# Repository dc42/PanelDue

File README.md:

PanelDue
========

This is the OLD source code for firmware versions 1.15x and earlier to run the PanelDue 3D printer user interface board. Source code for firmware versions 1.16 and later is in repository PanelDueFirmware, see https://github.com/dc42/PanelDueFirmware.

Build instructions: load file PanelDue.cppproj into Atmel Studio 7.0. For those wishing to build it under operating systems other than Windows, it should not be difficult to port it to Eclipse. The only libraries needed that are not included in this repository are the GCC toolchain libraries for the SAM3S.

Static analysis: parts of the firmware are formally verified using Escher C++ Verifier, hence the design-by-contract and other annotations. File ecv.h defines macros that make these annotations invisible to compilers.

Firmware upload instructions: see http://miscsolutions.wordpress.com/paneldue/

Licence and copyright
=====================

Copyright (c) 2015 Escher Technologies Limited. Licensed under the Creative Commons Attribution-NonCommercial 4.0 license. See https://creativecommons.org/licenses/by-nc/4.0/legalcode for a copy. Some parts of the firmware (c) Henning Karlsen. Some parts of the firmware (c) Atmel Inc.

Submitting pull requests
========================

I will only consider pull requests that meet the following standards:
- the code must compile warning-free, with very few exceptions
- existing design-by-contract annotations must be preserved, and contracts should be added for any new functions. Please asked for a copy of eCv++ Free Edition if you plan on making substantial changes.
- the coding style must be adhered to

Acknowledgements
================

Henning Karlsen - for the original versions of the TFT display driver, see http://www.henningkarlsen.com/electronics/
Atmel - for the Atmel Software Framework, which made programming the ATSAM3S a lot easier
MikroElectronika - for providing GLCD Font Creator, see http://www.mikroe.com/glcd-font-creator/
Andy (kwikius) - for writing a program to compress fonts generated by GLCD Font Creator

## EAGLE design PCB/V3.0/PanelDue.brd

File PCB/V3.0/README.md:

This is the schematic for the version 3.0 standalone PanelDue controller board. The PaneDue 5i with integrated display uses the same circuitry for the part that interfaces to the Duet, with the following changes:
1. A different 3.3V regulator chip is used
2. Connector X4 has a different pinout. Numbering the pins from the left (with the adjacent X4 legend), the pin connections are:
* Pin 1: PB6 (intended for rotary encoder push button)
* Pin 2: PA2 (intended for rotary encoder A pin)
* Pin 3: PA3 (intended for rotary encoder B pin)
* Pin 4: +3.3V
* Pin 5: Ground (rotary encoder common pin)

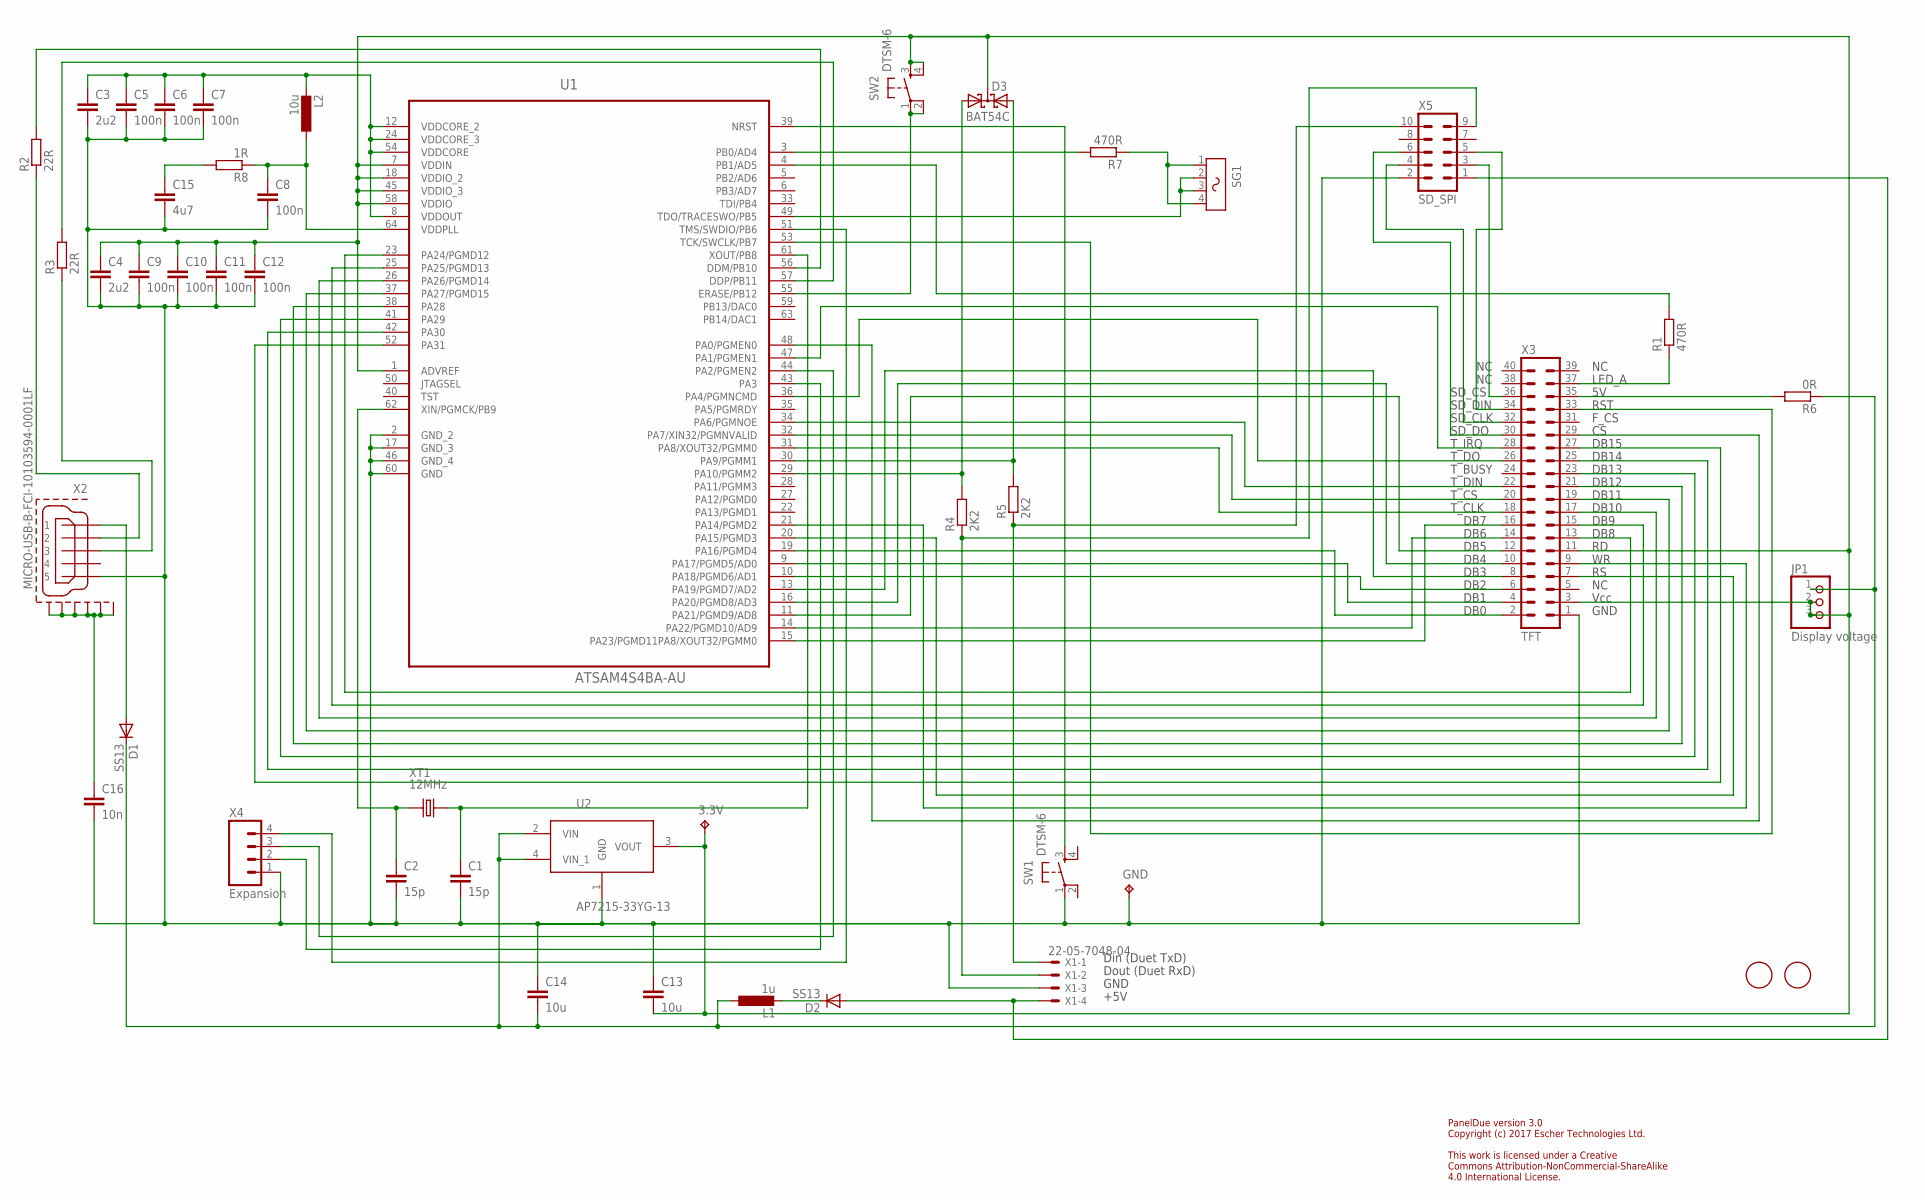
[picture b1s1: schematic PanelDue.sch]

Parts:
3.3V: TPPAD1-10; P1-10
C1, C2: 15p; C0603
C3, C4: 2u2; C0603
C5, C6, C7, C8, C9, C10, C11, C12: 100n; C0603
C13, C14: 10u; C0805
C15: 4u7; C0603
C16: 10n; C0603
D1, D2: SS13; DO214AC
D3: BAT54C; SOT23
GND: TPPAD1-10; P1-10
JP1: Display voltage; 1X03
L1: 1u; L2012C
L2: 10u; L2012C
R1, R7: 470R; R0603
R2, R3: 22R; R0603
R4, R5: 2K2; R0603
R6: 0R; R0603
R8: 1R; R0603
SG1: F/QMX2; F?QMX2
SW1, SW2: DTSM-6
U1: ATSAM4S4BA-AU; QFP50P1200X1200X160-64N
U2: AP7215-33YG-13; SOT150P400X160-4N
U$1, U$2: FIDUCIAL; FIDUCIAL_1MM
X1: 22-05-7048-04; 7395-04
X2: MICRO-USB-B-FCI-10103594-0001LF; 10103594-0001LF
X3: TFT; MA20-2
X4: Expansion; 1X04
X5: SD_SPI; ML10L
XT1: 12MHz; CRYSTAL-SMD-2PIN-5X3.2

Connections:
GND: C1.2, C2.2, C3.2, C4.2, C5.2, C6.2, C7.2, C8.2, C9.2, C10.2, C11.2, C12.2, C13.1, C14.1, C15.2, C16.2, GND.TP, SW1.1, U1.2 (GND_2), U1.17 (GND_3), U1.46 (GND_4), U1.60 (GND), U2.1 (GND), X1.3, X2.5, X3.1, X4.1, X5.2
unnamed: U1.19 (PA16/PGMD4), X3.2
unnamed: U1.31 (PA8/XOUT32/PGMM0), X3.18
unnamed: U1.9 (PA17/PGMD5/AD0), X3.4
unnamed: U1.10 (PA18/PGMD6/AD1), X3.6
unnamed: U1.16 (PA20/PGMD8/AD3), X3.10
unnamed: U1.14 (PA22/PGMD10/AD9), X3.14
unnamed: U1.11 (PA21/PGMD9/AD8), X3.12
unnamed: U1.15 (PA23/PGMD11PA8/XOUT32/PGMM0), X3.16
unnamed: U1.23 (PA24/PGMD12), X3.13
unnamed: U1.13 (PA19/PGMD7/AD2), X3.8
unnamed: U1.25 (PA25/PGMD13), X3.15
unnamed: U1.26 (PA26/PGMD14), X3.17
unnamed: U1.37 (PA27/PGMD15), X3.19
unnamed: U1.38 (PA28), X3.21
unnamed: U1.41 (PA29), X3.23
unnamed: U1.42 (PA30), X3.25
unnamed: U1.52 (PA31), X3.27
unnamed: R2.2, U1.56 (DDM/PB10)
unnamed: U1.34 (PA6/PGMNOE), X3.22
unnamed: U1.36 (PA4/PGMNCMD), X3.26
unnamed: C1.1, U1.61 (XOUT/PB8), XT1.P$2 (2)
unnamed: C2.1, U1.62 (XIN/PGMCK/PB9), XT1.P$1 (1)
unnamed: SW2.1, SW2.2, U1.55 (ERASE/PB12)
unnamed: C8.1, L2.1, R8.1, U1.64 (VDDPLL)
unnamed: SW1.3, U1.39 (NRST)
unnamed: D3.2 (A2), R5.2, U1.30 (PA9/PGMM1)
unnamed: D3.1 (A1), R4.2, U1.29 (PA10/PGMM2)
unnamed: R3.2, U1.57 (DDP/PB11)
unnamed: R4.1, X1.2, X5.9
unnamed: R5.1, X1.1, X5.10
unnamed: D1.A, X2.1
unnamed: R2.1, X2.2
unnamed: R7.2, U1.3 (PB0/AD4)
unnamed: R3.1, X2.3
unnamed: U1.32 (PA7/XIN32/PGMNVALID), X3.20
unnamed: U1.47 (PA1/PGMEN1), X3.28
unnamed: R1.1, X3.37
unnamed: X3.36, X5.3
unnamed: R7.1, SG1.1, SG1.4
unnamed: U1.43 (PA3), X4.2
unnamed: U1.44 (PA2/PGMEN2), X4.3
unnamed: U1.53 (TCK/SWCLK/PB7), X3.33
unnamed: U1.48 (PA0/PGMEN0), X3.29
unnamed: U1.21 (PA14/PGMD2), X3.9
unnamed: D2.C, L1.2
unnamed: C16.1, X2.GND1, X2.GND2, X2.GND3, X2.GND4, X2.GND5, X2.GND6
unnamed: U1.20 (PA15/PGMD3), X3.7
unnamed: C15.1, R8.2
unnamed: D2.A, X1.4, X5.1
unnamed: X3.34, X5.5
unnamed: R1.2, U1.4 (PB1/AD5)
unnamed: U1.51 (TMS/SWDIO/PB6), X4.4
unnamed: SG1.2, SG1.3, U1.49 (TDO/TRACESWO/PB5)
unnamed: C3.1, C5.1, C6.1, C7.1, L2.2, U1.8 (VDDOUT), U1.12 (VDDCORE_2), U1.24 (VDDCORE_3), U1.54 (VDDCORE)
unnamed: X3.32, X5.4
unnamed: X3.30, X5.6
unnamed: R6.2, X3.35
VCC: 3.3V.TP, C4.1, C9.1, C10.1, C11.1, C12.1, C13.2, D3.3 (CC), JP1.2, JP1.3, SW2.3, SW2.4, U1.1 (ADVREF), U1.7 (VDDIN), U1.18 (VDDIO_2), U1.45 (VDDIO_3), U1.58 (VDDIO), U2.3 (VOUT), X3.3, X3.11
VCC5: C14.2, D1.C, JP1.1, L1.1, R6.1, U2.2 (VIN), U2.4 (VIN_1)

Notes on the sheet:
T_BUSY
SD_CS
SD_DIN
SD_CLK
SD_DO
T_IRQ
GND
Vcc
DB0
DB1
DB2
DB3
DB4
DB5
DB6
DB7
T_CLK
T_CS
T_DIN
T_DO
DB8
DB9
DB10
DB11
DB12
DB13
DB14
DB15
F_CS
RST
LED_A
+5V
Dout (Duet RxD)
Din (Duet TxD)
PanelDue version 3.0 Copyright (c) 2017 Escher Technologies Ltd. This work is licensed under a Creative Commons Attribution-NonCommercial-ShareAlike 4.0 International License.

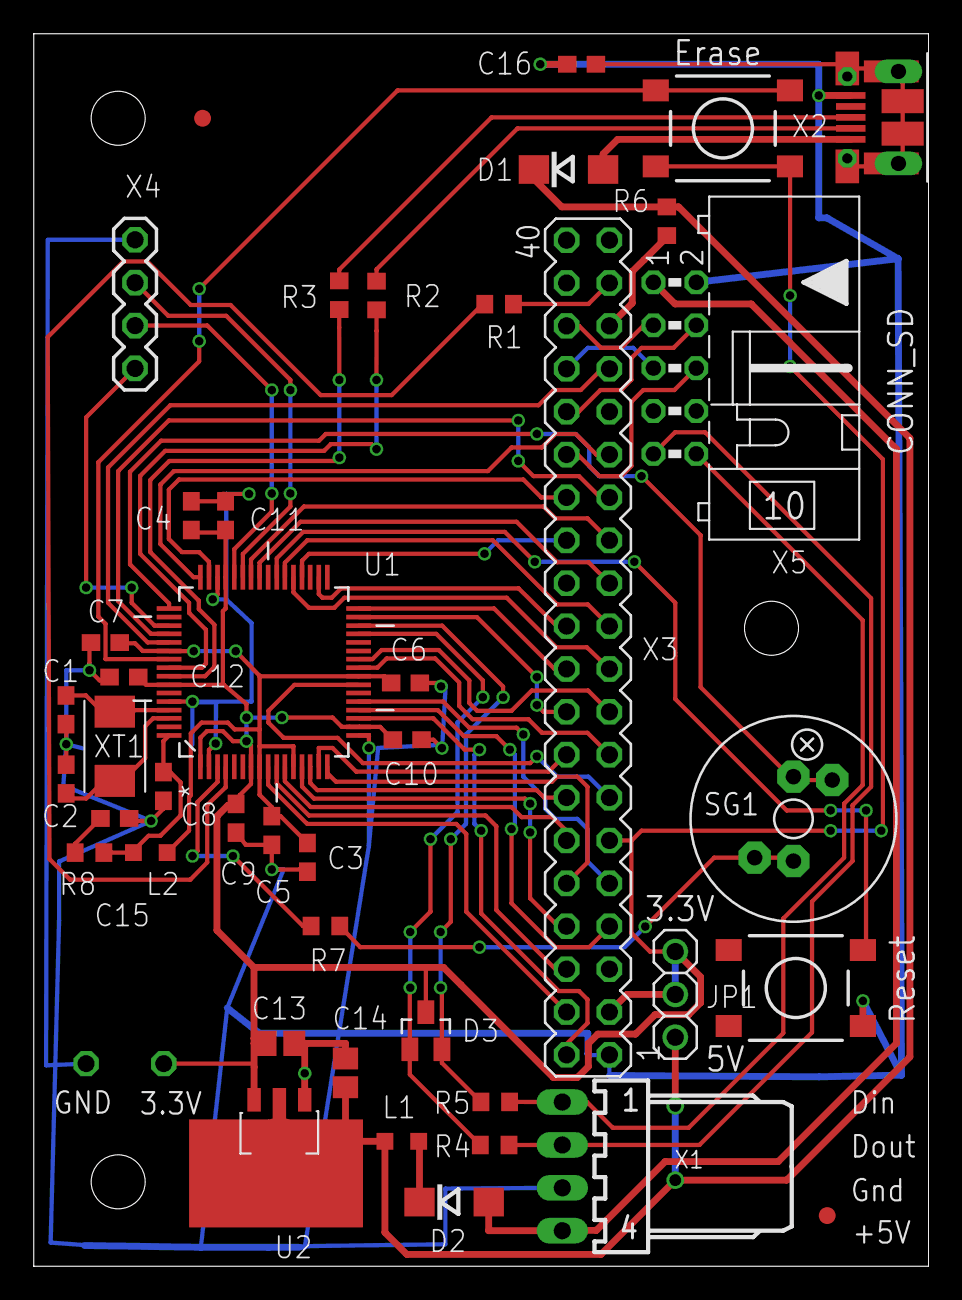
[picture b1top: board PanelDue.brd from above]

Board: 2 copper layers, 53.0 x 73.0 mm, 45 parts (0 on the bottom side), 60 nets.

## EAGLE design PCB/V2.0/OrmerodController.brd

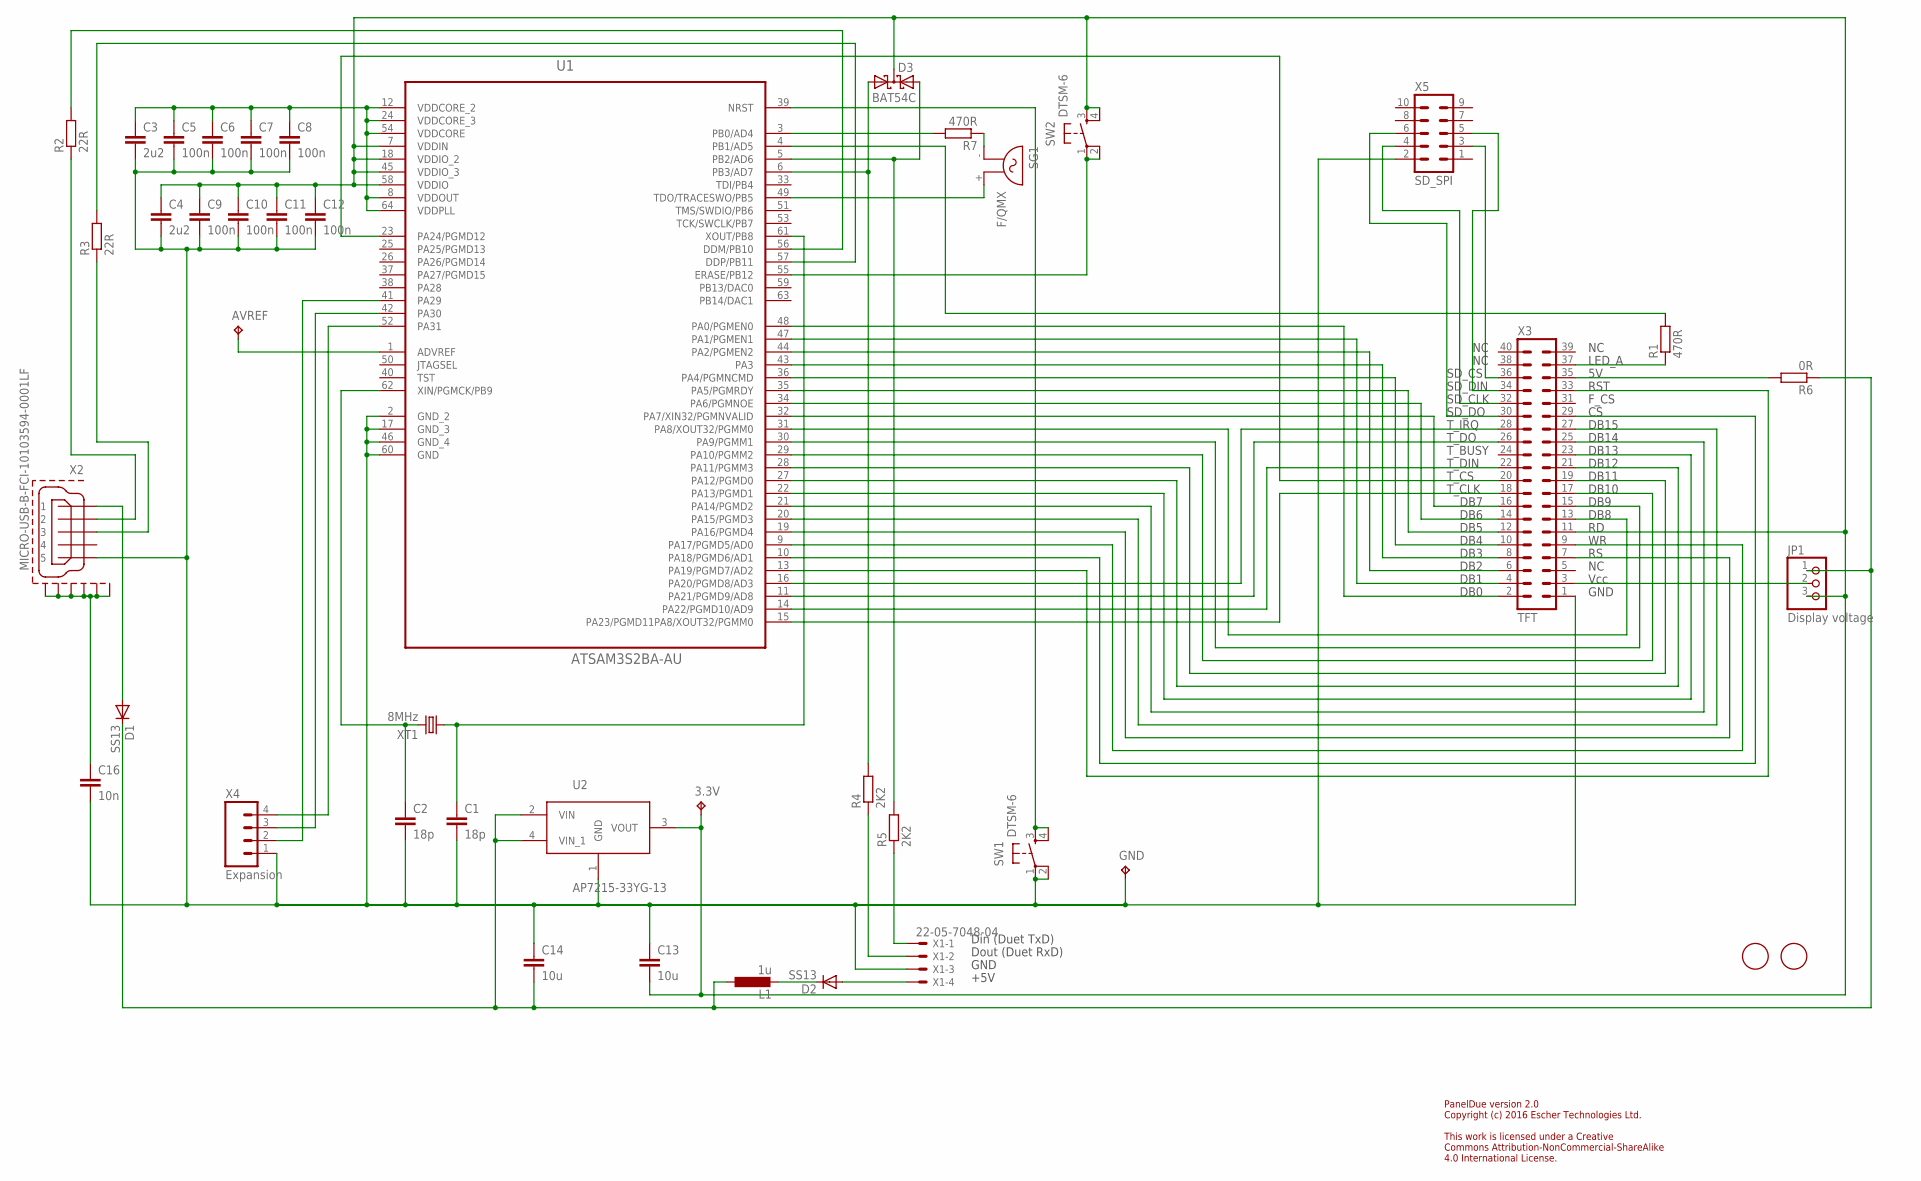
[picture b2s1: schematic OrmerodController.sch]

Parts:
3.3V: TPPAD1-10; P1-10
AVREF: TPPAD1-10; P1-10
C1, C2: 18p; C0603
C3, C4: 2u2; C0603
C5, C6, C7, C8, C9, C10, C11, C12: 100n; C0603
C13, C14: 10u; C0805
C16: 10n; C0603
D1, D2: SS13; DO214AC
D3: BAT54C; SOT23
GND: TPPAD1-10; P1-10
JP1: Display voltage; 1X03
L1: 1u; L2012C
R1, R7: 470R; R0603
R2, R3: 22R; R0603
R4, R5: 2K2; R0603
R6: 0R; R0603
SG1: F/QMX
SW1, SW2: DTSM-6
U1: ATSAM3S2BA-AU; QFP50P1200X1200X160-64N
U2: AP7215-33YG-13; SOT150P400X160-4N
U$1, U$2: FIDUCIAL; FIDUCIAL_1MM
X1: 22-05-7048-04; 7395-04
X2: MICRO-USB-B-FCI-10103594-0001LF; 10103594-0001LF
X3: TFT; MA20-2
X4: Expansion; 1X04
X5: SD_SPI; ML10L
XT1: 8MHz; HC49UP

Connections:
GND: C1.2, C2.2, C3.2, C4.2, C5.2, C6.2, C7.2, C8.2, C9.2, C10.2, C11.2, C12.2, C13.1, C14.1, C16.2, GND.TP, SW1.1, SW1.2, U1.2 (GND_2), U1.17 (GND_3), U1.46 (GND_4), U1.60 (GND), U2.1 (GND), X1.3, X2.5, X3.1, X4.1, X5.2
unnamed: U1.48 (PA0/PGMEN0), X3.2
unnamed: U1.15 (PA23/PGMD11PA8/XOUT32/PGMM0), X3.18
unnamed: U1.47 (PA1/PGMEN1), X3.4
unnamed: U1.44 (PA2/PGMEN2), X3.6
unnamed: U1.36 (PA4/PGMNCMD), X3.10
unnamed: U1.34 (PA6/PGMNOE), X3.14
unnamed: U1.35 (PA5/PGMRDY), X3.12
unnamed: U1.32 (PA7/XIN32/PGMNVALID), X3.16
unnamed: U1.31 (PA8/XOUT32/PGMM0), X3.13
unnamed: U1.43 (PA3), X3.8
unnamed: U1.30 (PA9/PGMM1), X3.15
unnamed: U1.29 (PA10/PGMM2), X3.17
unnamed: U1.28 (PA11/PGMM3), X3.19
unnamed: U1.27 (PA12/PGMD0), X3.21
unnamed: U1.22 (PA13/PGMD1), X3.23
unnamed: U1.21 (PA14/PGMD2), X3.25
unnamed: U1.20 (PA15/PGMD3), X3.27
unnamed: R2.2, U1.56 (DDM/PB10)
unnamed: U1.14 (PA22/PGMD10/AD9), X3.22
unnamed: U1.11 (PA21/PGMD9/AD8), X3.26
unnamed: C1.1, U1.61 (XOUT/PB8), XT1.1
unnamed: C2.1, U1.62 (XIN/PGMCK/PB9), XT1.2
unnamed: SW2.1, SW2.2, U1.55 (ERASE/PB12)
unnamed: U1.41 (PA29), X4.2
unnamed: SW1.3, SW1.4, U1.39 (NRST)
unnamed: D3.2 (A2), R5.2, U1.5 (PB2/AD6)
unnamed: D3.1 (A1), R4.2, U1.6 (PB3/AD7)
unnamed: R3.2, U1.57 (DDP/PB11)
unnamed: R4.1, X1.2
unnamed: R5.1, X1.1
unnamed: D1.A, X2.1
unnamed: R2.1, X2.2
unnamed: R7.2, U1.3 (PB0/AD4)
unnamed: R3.1, X2.3
unnamed: U1.23 (PA24/PGMD12), X3.20
unnamed: U1.16 (PA20/PGMD8/AD3), X3.28
unnamed: JP1.2, X3.3
unnamed: R1.1, X3.37
unnamed: X3.36, X5.3
unnamed: R7.1, SG1.- (1)
unnamed: U1.42 (PA30), X4.3
unnamed: U1.52 (PA31), X4.4
unnamed: U1.13 (PA19/PGMD7/AD2), X3.33
unnamed: U1.10 (PA18/PGMD6/AD1), X3.29
unnamed: U1.9 (PA17/PGMD5/AD0), X3.9
unnamed: D2.C, L1.2
unnamed: C16.1, X2.GND1, X2.GND2, X2.GND3, X2.GND4, X2.GND5, X2.GND6
unnamed: U1.19 (PA16/PGMD4), X3.7
unnamed: AVREF.TP, U1.1 (ADVREF)
unnamed: D2.A, X1.4
unnamed: X3.34, X5.5
unnamed: R1.2, U1.4 (PB1/AD5)
unnamed: SG1.+ (2), U1.49 (TDO/TRACESWO/PB5)
unnamed: C3.1, C5.1, C6.1, C7.1, C8.1, U1.8 (VDDOUT), U1.12 (VDDCORE_2), U1.24 (VDDCORE_3), U1.54 (VDDCORE), U1.64 (VDDPLL)
unnamed: X3.32, X5.4
unnamed: X3.30, X5.6
unnamed: R6.2, X3.35
VCC: 3.3V.TP, C4.1, C9.1, C10.1, C11.1, C12.1, C13.2, D3.3 (CC), JP1.3, SW2.3, SW2.4, U1.7 (VDDIN), U1.18 (VDDIO_2), U1.45 (VDDIO_3), U1.58 (VDDIO), U2.3 (VOUT), X3.11
VCC5: C14.2, D1.C, JP1.1, L1.1, R6.1, U2.2 (VIN), U2.4 (VIN_1)

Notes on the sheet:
T_BUSY
SD_CS
SD_DIN
SD_CLK
SD_DO
T_IRQ
GND
Vcc
DB0
DB1
DB2
DB3
DB4
DB5
DB6
DB7
T_CLK
T_CS
T_DIN
T_DO
DB8
DB9
DB10
DB11
DB12
DB13
DB14
DB15
F_CS
RST
LED_A
+5V
Dout (Duet RxD)
Din (Duet TxD)
PanelDue version 2.0 Copyright (c) 2016 Escher Technologies Ltd. This work is licensed under a Creative Commons Attribution-NonCommercial-ShareAlike 4.0 International License.

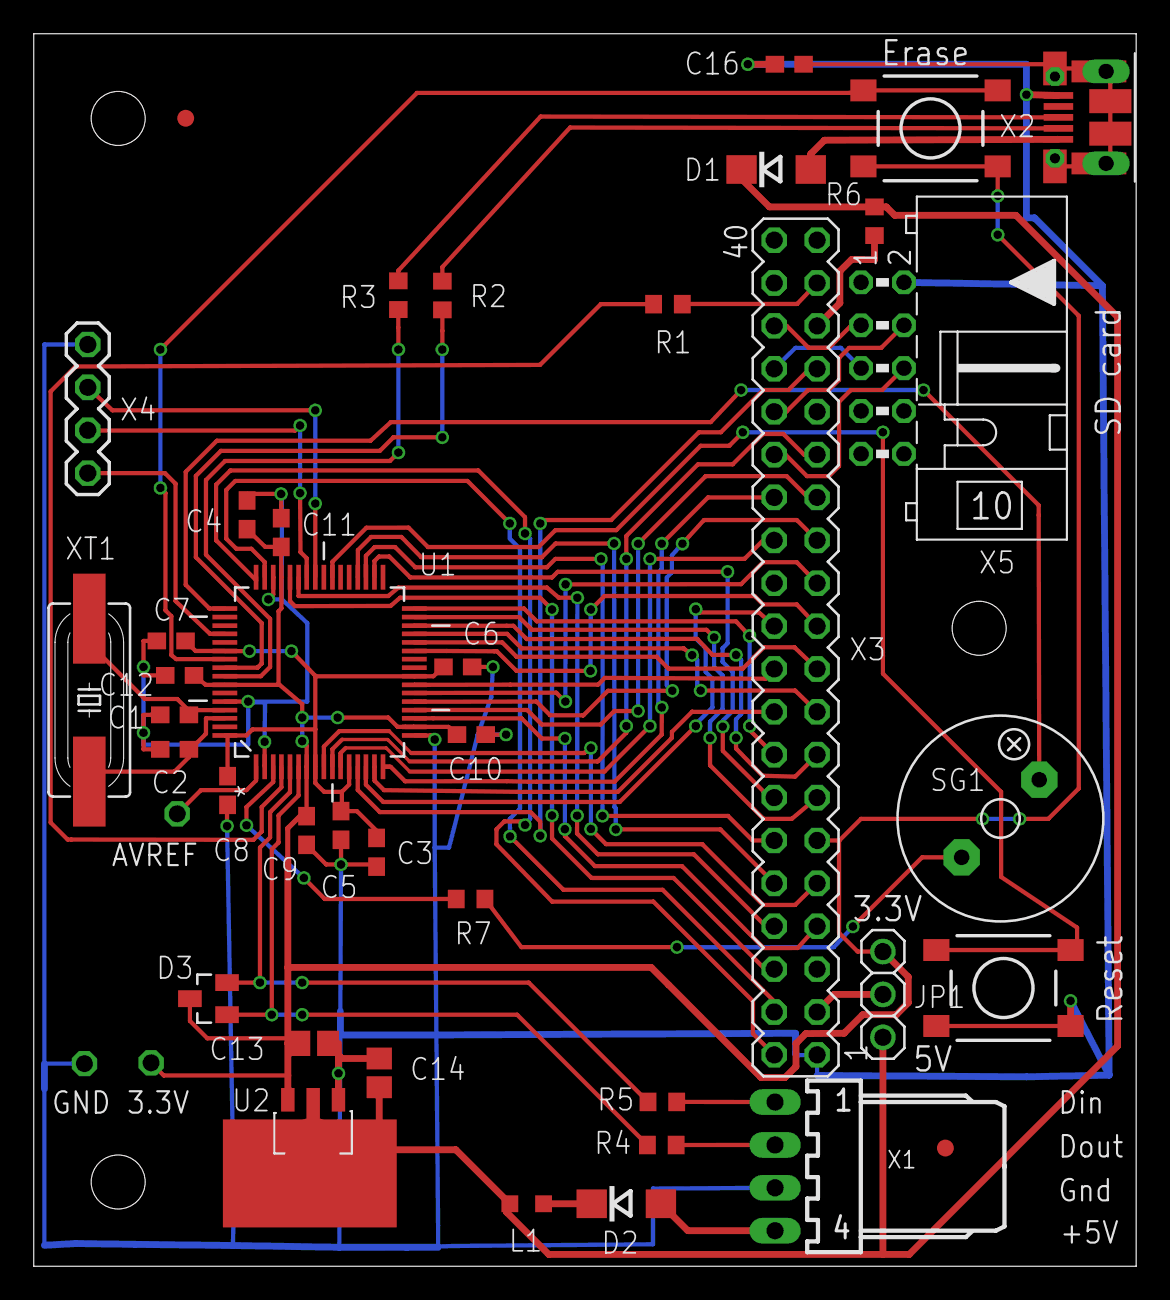
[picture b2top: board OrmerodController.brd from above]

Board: 2 copper layers, 65.3 x 73.0 mm, 43 parts (0 on the bottom side), 60 nets.

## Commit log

2014-11-06 :circus_tent: Added .gitattributes
2014-11-08 Started adding UART support
2014-11-10 Added serial I/O interface
2014-11-13 More on processing received data
2014-11-13 Added beep feedback for touch interface
2014-11-14 Added more fields and improved beep
2014-11-14 Added touch calibration
    Added touch calibration function. Not saved to flash memory yet.
2014-11-14 Various fixes and improvements
2014-11-24 Added ability to move the print head
2014-11-25 Added file list and file print
2014-12-03 4.3 inch display support and more functionality
    Added support for 4.3 inch display. Added more functionality including
    beep support.
2014-12-06 Renamed project to PanelDue and added binaries
2014-12-09 Added partial support for 5 inch display
2014-12-18 Fixed problem with touch driver
    Fixed a problem whereby the touch driver sometimes reported inaccurate
    positions
2015-01-09 Added more binaries
2015-01-11 Corrected free memory readout
2015-01-15 Self-adjusting touch panel orientation
2015-01-16 Fixed flash write code + other changes
    Fixed the flash memory write function
    Fixed auto touch orientation determination
    Renamed Info tab to Setup
    Added firmware version to Setup tab
    Corrected code for C++11
2015-01-24 Added enclosure
    Added enclosure files (thanks appjaws1 and dmould). LCD cutouts and
    mounting points should be correct for the low-cost 4.3 inch display, but
    the controller PCB mounting positions, reset and erase button holes, and
    USB connector hole still need sorting out.
2015-01-27 Version 1.01
    Temperatures, speeds and extrusion factors can now be adjusted in steps
    of 1 and
    Adjusted temperatures start art zero if they are initially negative
    Fixed touch accuracy error
    File list is now sorted and scrollable
    Added factory reset button
2015-01-28 Finished basic design, support 3 display types
    Now has correct PCB dimensions and supports 3 types of display
2015-01-29 Corrected design and renamed files
2015-01-30 Added 57600 baud binary
2015-01-31 Version 1.02
    Added option to invert display
    Baud rate is now selectable, default 57600b
    Checksum now added to all messages
    Added quick commands on Control page
2015-02-01 Fix Typo on Control screen
2015-02-07 Version 1.03
    Corrected typo in quick commands
    SD card files can now be deleted
    Added "Are you sure?" dialog
    Beep volume can be adjusted
    Separate button to save settings
    Show baud rate on Settings screen
2015-02-10 Updated .pdp file, added cheatic
2015-02-21 Version 1.04
    Added message log
    Added print pause/resume/cancel buttons
    Added print time estimates
2015-02-21 Removed some binaries, updated source
2015-02-21 Added version 1.04 binary
2015-02-24 Version 1.05
    Fixed issue with not being able to set beep volume
    Improved display of print time remaining
    Fetch filename if a print is started from another source, or already in
    progress when PanelDue is reset
2015-02-27 Version 1.06
    Implemented macros
    Minor layout changes
    Switch to printing page if PanelDue is started when the printer is
    printing or paused
2015-03-04 Interim checking for version 1.07
    Re-did 19x20 font as 19x21 to include all of Latin-1 character set
    Translate from UTF8 to Latin-1 when writing to display
    Added 28x32 font and text positioning for 5 inch display (not tested
    yet)
2015-03-04 Version 1.07
    Added support for UTF8 code points 0xA0 to 0xFF, by generating new fonts
    and translating fro UTF8 in display driver
    Support 5 inch screen properly by adding 28x32 font and adjusting field
    positions
    Bug fix: after re-running touch calibration, the user was not warned
    that settings were not saved
2015-03-24 Version 1.08
    Tool numbers are now assumed to be T0 and T1 instead of T1 and T2
    Improved spacing of macro buttons on 5 inch display
    Increased max length of "Generated by" text for 5 inch display
2015-03-25 Renamed binaries to 1.09 because that's what they c
    Renamed binaries to 1.09 because that's the version displayed on the
    Setup page
2015-04-09 Updated enclosure model
    Changed to enclosure model:
    - Wall thickness increased to 2.4mm for compatibility with slic3r
    default extrusion width on 0.5mm Ormerod
    - Pillar diameter increased to improve strength
    - Holes for self tapping screws increased to 2.2mm
    - Guide tubes added for Reset and Erase buttons
2015-07-26 Added production PCB files
2015-08-30 Version 1.10
    Changed appearance to be slightly less antique
    Fixed file delete problem
    Bed comp or auto cal button now displayed with the homing buttons
2015-09-02 Version 1.11
    Improved touch accuracy
2015-10-10 Version 1.11a
    Increment line number for each command sent
    Changes for eCv++ compatibility
2015-10-23 Added option for alternative 5 inch display
2015-10-24 Interim version
    Added support for icon buttons
    Refactored DisplayField and Button classes
    Moved fonts to separate folder
    Converted to Atmel Studio 7
2015-10-31 Corrected visible area for alt 5 inch display
2015-10-31 Updated STL for alt 5 inch display
2015-11-08 Version 1.12 beta 1
    Changed some buttons to have icons instead of text.
    Support up to 4 hot ends on the 4.3 and 6 hot ends on the 5 inch
    display.
    Gcode file list is now a popup,. Uses the same one for macros.
    Added keyboard for entering gcodes.
    Added language configuration.
2015-11-10 Added bmp2c,ini file
2015-11-11 Version 1.12 beta 2
    Keyboard not at top of Console window. Messages scroll in from bottom of
    Console window instead of top.
    Added command history buffer.
    Use more icons.
2015-11-15 Refactoring and more icons
2015-11-17 Version 1.12 beta 3
    Added more icons
    Got progress bar displaying again
    Added support for 7 inch display
2015-11-18 Version 1.12
    Improved touch behaviour, in particular for 7" display
    Allow fan speed setting to be cancelled
2015-11-25 Version 1.13 beta 1
    Added Extrude popup
    Support subdirectories in macro and file lists
    Ignore empty messages
    Allow a different page to be selected even when there is a popup.
    Preserve keyboard popup.
    Allow other options on Settings tab to be pressed even if there is
2015-11-30 Added 7" display and increased USB cutout size
    Added dimension for the 7 inch display
    Increase size of USB cutout to take a USB plug
    Increase hole sizes for PCB and LCD mounts
2015-12-06 Version 1.13
    Fixed issue with repeated sending of M20 command
    Improved the way that the command history works
    Improved the home icons
    Pick up the fan speed form the M408 status response, if present
2016-01-23 Added 7 inch option to enclosure design
2016-02-12 Minor changes to enclosure model
2016-02-24 Updated readme file
2016-06-12 Version 1.14
    Implemented alert messages (M117)
    Added new state for firmware update
    Added ':' key to keyboard
    Close buttons are now always placed in the top right hand corner of the
    window
    Layer height is now displayed to 2 decimal places
2016-09-05 Version 1.15 beta 2
    Added support for multiple colour schemes - not yet complete because we
    need icons with palettes to finish this
    Improved layout of file intormation popup
    Improved keyboard layout
    Clear popups when reconnected after firmware update
    Moved SD card icon to first page
2016-09-06 Version 1.15 beta 3
    Adjusted keyboard size so that 2 rows of console output are visible on
    the 4.3 inch display
2016-09-08 Updated enclosures
    Updated enclosures for board version 2.0
2016-10-19 Version 1.15
    Added support for U axis on 4.3 and U,V,W axes on 5 and 7 inch screens
    Allow more than 3 heaters to be displayed
    Speed up drawing of graphics
2016-10-21 Release 1.15a
    Show U,V,W axis positions if these axes are present
    Increased backlight PWM frequency to 250Hz to reduce flicker on 4.3"
    screen
2016-10-22 Version 1.15b
    Bug fix: on the 7 inch panel, if you inverted or morrired the display,
    the colours were wrong until the next reboot
    Optimise all builds for code space
2016-10-23 Version 1.15c
    Corrected touch spot colours when dark theme is used
    Presisng bed tool button now switchws the bed heater between active and
    standby
2016-11-21 Small refactoring to better support multiple OEMs
2016-11-22 Support OEM splash screens on 4.3" panels
2017-01-04 Updated enclosure model
2017-01-12 Added v2.0 schematic and up-dated enclosure model
2017-01-15 Replace definition of OPTIMIZE_HIGH
    Replace erroneous definition of OPTIMIZE_HIGH for latest version of GCC.
2017-03-23 Added version 2.0 files
2017-06-19 Corrected schematic, removed binaries
    Corrected crystal frequency in schematic
    Removed old binaries
2017-08-27 Corrected lid in PanelDueEnclosure.scad
2017-09-17 Added version 3 schematic and PCB
2020-03-13 Added README file
    Added README file describing PanelDue 5i differences

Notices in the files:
parts and their libraries:
SparkFun-Connectors: Licensing: CC v3.0 Share-Alike You are welcome to use this library for commercial purposes.
